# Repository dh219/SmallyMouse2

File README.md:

## Synopsis

SmallyMouse2 is the AT90USB1287 firmware source code and KiCAD schematic/PCB design for the SmallyMouse2 project.

Smalliermouse is a variation of SmallyMouse2 by D Henderson specificially designed for the Atari ST & Falcon to fit within the keyboard mouse plug bay.

## Motivation

SmallyMouse2 is a project that creates a USB mouse adaptor for retro computers that use quadrature mouse input including the Acorn BBC Micro, Acorn Master series, Commodore Amiga, Atari ST, busmouse compatible computers and many more.  SmallyMouse2 provides both a generic mouse output header (for attaching mouse to retro computer cables) and an IDC connector suitable for use with Acorn 8-bit user-ports.  SmallyMouse2 also features a configurable quadrature rate limiter that prevents VIA overrun when in use with slower 8-bit machines.

SmallyMouse2 supports both JTAG and USB bootloader programming.  The AT90USB1287 is pre-programmed by Atmel with the (FLIP) DFU bootloader; this bootloader is recognised by Atmel Studio as a programming device and can be used to flash the firmware to the board.

## Installation

Note: This is an Atmel Studio 7 project that can be loaded and compiled by the IDE

Please see http://www.waitingforfriday.com/?p=827 for detailed documentation about SmallyMouse2

## Author

SmallyMouse2 is written and maintained by Simon Inns

## License (Software)

    SmallyMouse2 is free software: you can redistribute it and/or modify
    it under the terms of the GNU General Public License as published by
    the Free Software Foundation, either version 3 of the License, or
    (at your option) any later version.

    SmallyMouse2 is distributed in the hope that it will be useful,
    but WITHOUT ANY WARRANTY; without even the implied warranty of
    MERCHANTABILITY or FITNESS FOR A PARTICULAR PURPOSE.  See the
    GNU General Public License for more details.

    You should have received a copy of the GNU General Public License
    along with SmallyMouse2. If not, see <http://www.gnu.org/licenses/>.

## License (Hardware)

Both the schematic and the PCB design of SmallyMouse2 (i.e. the KiCAD project and files) are covered by a Creative Commons license; as with the software you are welcome (and encouraged!) to extend, re-spin and otherwise use and modify the design as allowed by the license.  However; under the terms of the Attribution-ShareAlike 4.0 International (CC BY-SA 4.0) license you are required to release your design (or redesign) under the same license.  For details of the licensing requirements please see <https://creativecommons.org/licenses/by-sa/4.0/>

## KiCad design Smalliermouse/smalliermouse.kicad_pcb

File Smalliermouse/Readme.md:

## Synopsis

Smalliermouse is a variation of SmallyMouse2 by D Henderson specificially designed for the Atari ST & Falcon to fit within the keyboard mouse plug bay.

## Motivation

USB plugs for modern (and particularly wireless) devices are so small theses days that, buy reducing the SmallyMouse2 footprint to its bare minimum would allow the entire mouse emulator to fit within the below-keyboard recess of the Atari ST range of computers.

## Installation

Note: This is an Atmel Studio 7 project that can be loaded and compiled by the IDE

Please see http://www.waitingforfriday.com/?p=827 for detailed documentation about SmallyMouse2

## Author

SmallyMouse2 is written and maintained by Simon Inns. Smalliermouse, upon which it is based remains (C) Simon Inns with modifications by D Henderson 2019.

## License (Software)

    SmallyMouse2 is free software: you can redistribute it and/or modify
    it under the terms of the GNU General Public License as published by
    the Free Software Foundation, either version 3 of the License, or
    (at your option) any later version.

    SmallyMouse2 is distributed in the hope that it will be useful,
    but WITHOUT ANY WARRANTY; without even the implied warranty of
    MERCHANTABILITY or FITNESS FOR A PARTICULAR PURPOSE.  See the
    GNU General Public License for more details.

    You should have received a copy of the GNU General Public License
    along with SmallyMouse2. If not, see <http://www.gnu.org/licenses/>.

## License (Hardware)

Both the schematic and the PCB design of SmallyMouse2 (i.e. the KiCAD project and files) are covered by a Creative Commons license; as with the software you are welcome (and encouraged!) to extend, re-spin and otherwise use and modify the design as allowed by the license.  However; under the terms of the Attribution-ShareAlike 4.0 International (CC BY-SA 4.0) license you are required to release your design (or redesign) under the same license.  For details of the licensing requirements please see <https://creativecommons.org/licenses/by-sa/4.0/>

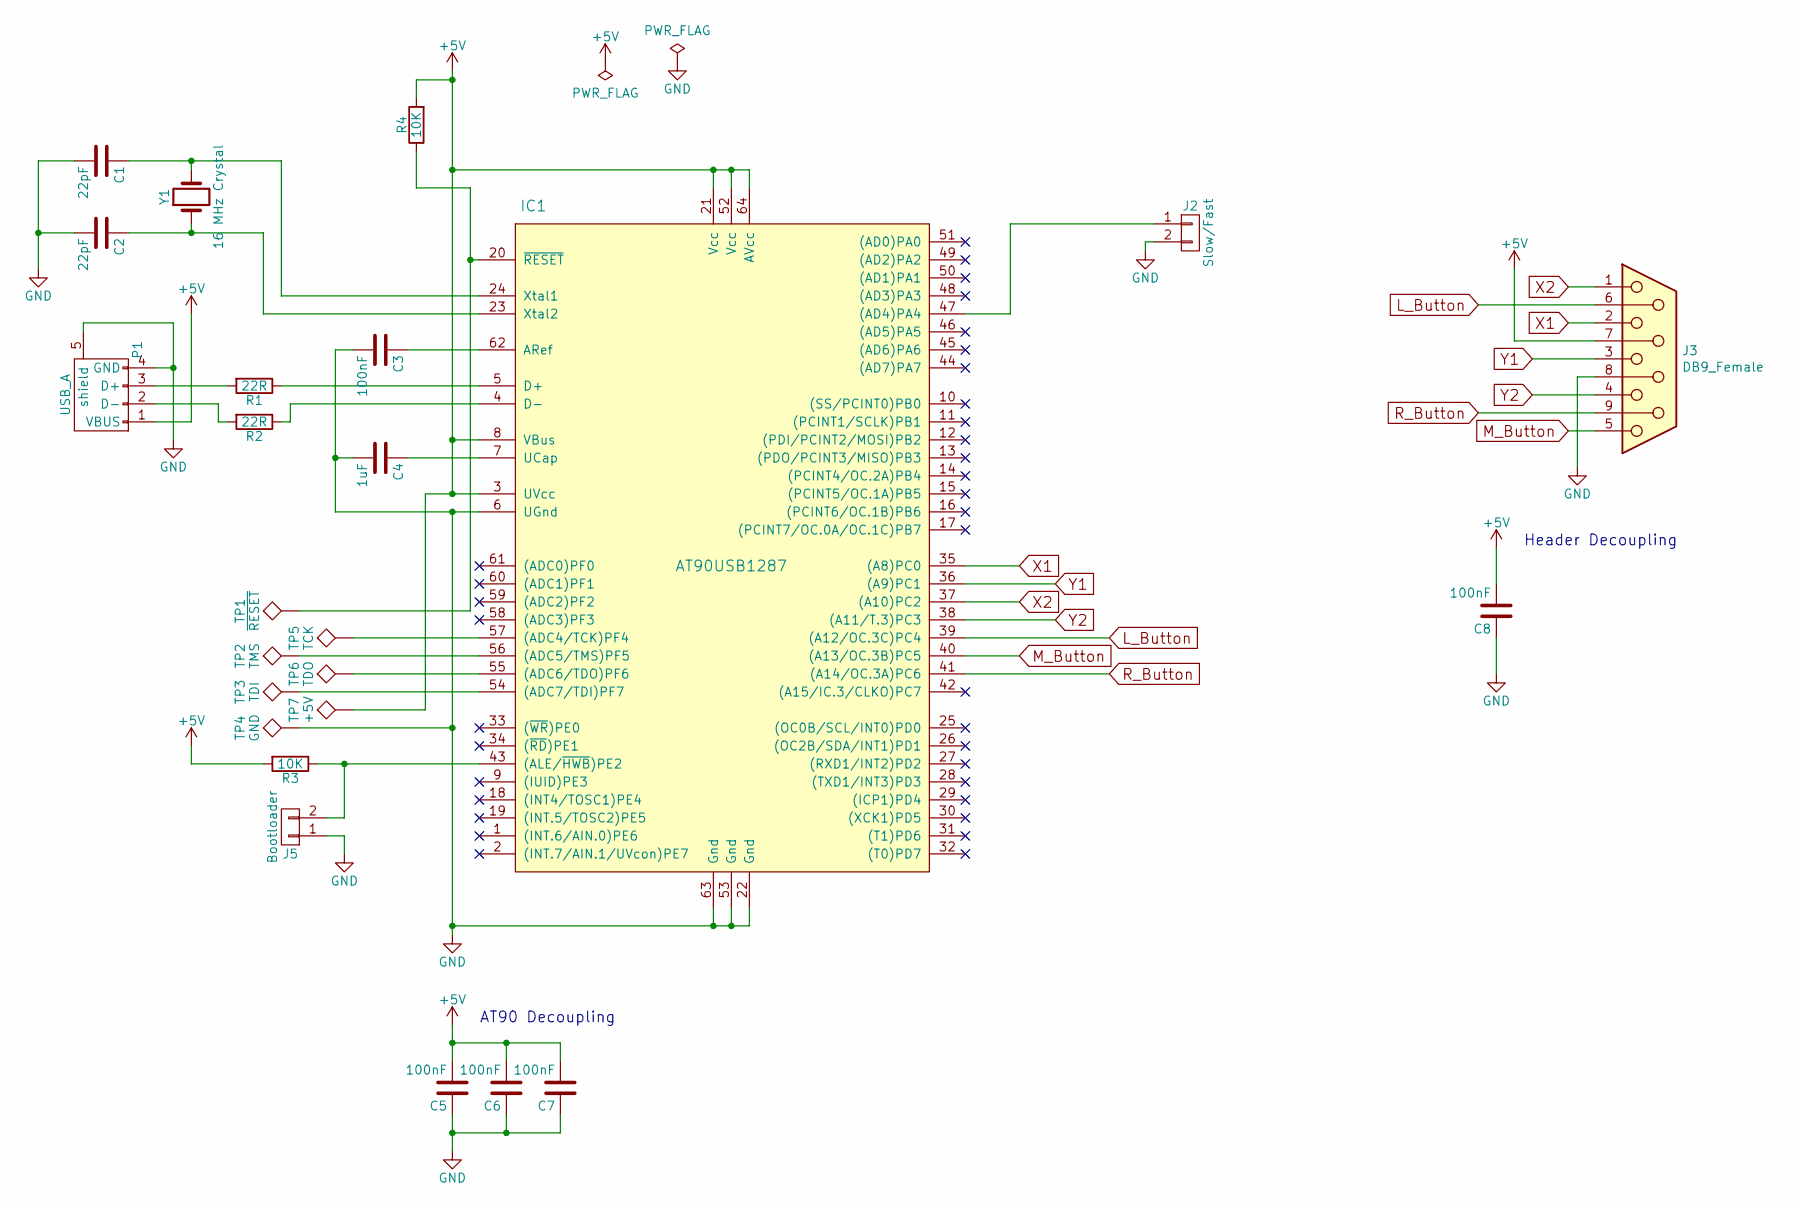
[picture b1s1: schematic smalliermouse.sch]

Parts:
C1, C2: 22pF; C_0805_2012Metric_Pad1.15x1.40mm_HandSolder
C3, C5, C6, C7, C8: 100nF; C_0805_2012Metric_Pad1.15x1.40mm_HandSolder
C4: 1uF; C_0805_2012Metric_Pad1.15x1.40mm_HandSolder
IC1: AT90USB1287; TQFP-64_14x14mm_P0.8mm
J2: Slow/Fast; PinHeader_1x02_P2.54mm_Vertical
J3: DB9_Female; DSUB-9_Female_EdgeMount_P2.77mm
J5: Bootloader; PinHeader_1x02_P2.54mm_Vertical
P1: USB_A; USB_A_CNCTech_1001-011-01101_Horizontal
R1, R2: 22R; R_0805_2012Metric_Pad1.15x1.40mm_HandSolder
R3, R4: 10K; R_0805_2012Metric_Pad1.15x1.40mm_HandSolder
TP1: ~RESET; TestPoint_Pad_1.0x1.0mm
TP2: TMS; TestPoint_Pad_1.0x1.0mm
TP3: TDI; TestPoint_Pad_1.0x1.0mm
TP4: GND; TestPoint_Pad_1.0x1.0mm
TP5: TCK; TestPoint_Pad_1.0x1.0mm
TP6: TDO; TestPoint_Pad_1.0x1.0mm
TP7: +5V; TestPoint_Pad_1.0x1.0mm
Y1: 16 MHz Crystal; Crystal_SMD_5032-2Pin_5.0x3.2mm_HandSoldering

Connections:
+5V: C5.2, C6.2, C7.2, C8.2, IC1.3 (UVcc), IC1.8 (VBus), IC1.21 (Vcc), IC1.52 (Vcc), IC1.64 (AVcc), J3.7, P1.1 (VBUS), R3.2, R4.2, TP7.1
GND: C1.2, C2.2, C3.2, C4.2, C5.1, C6.1, C7.1, C8.1, IC1.6 (UGnd), IC1.22 (Gnd), IC1.53 (Gnd), IC1.63 (Gnd), J2.2, J3.8, J5.1, P1.4 (GND), P1.5 (shield), TP4.1
L_Button: IC1.39 ((A12/OC.3C)PC4), J3.6
M_Button: IC1.40 ((A13/OC.3B)PC5), J3.5
unnamed: C1.1, IC1.24 (Xtal1), Y1.2
unnamed: C2.1, IC1.23 (Xtal2), Y1.1
unnamed: C3.1, IC1.62 (ARef)
unnamed: C4.1, IC1.7 (UCap)
unnamed: IC1.4 (D-), R2.1
unnamed: IC1.5 (D+), R1.1
unnamed: IC1.20 (~RESET), R4.1, TP1.1
unnamed: IC1.43 ((ALE/~HWB~)PE2), J5.2, R3.1
unnamed: IC1.47 ((AD4)PA4), J2.1
unnamed: IC1.54 ((ADC7/TDI)PF7), TP3.1
unnamed: IC1.55 ((ADC6/TDO)PF6), TP6.1
unnamed: IC1.56 ((ADC5/TMS)PF5), TP2.1
unnamed: IC1.57 ((ADC4/TCK)PF4), TP5.1
unnamed: P1.2 (D-), R2.2
unnamed: P1.3 (D+), R1.2
R_Button: IC1.41 ((A14/OC.3A)PC6), J3.9
X1: IC1.35 ((A8)PC0), J3.2
X2: IC1.37 ((A10)PC2), J3.1
Y1: IC1.36 ((A9)PC1), J3.3
Y2: IC1.38 ((A11/T.3)PC3), J3.4

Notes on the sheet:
AT90 Decoupling
Header Decoupling

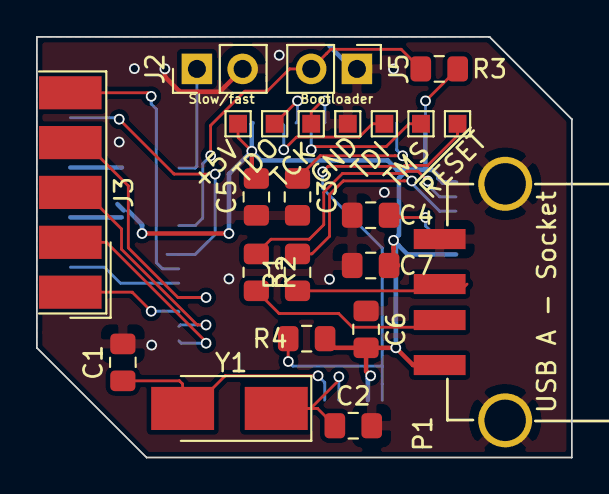
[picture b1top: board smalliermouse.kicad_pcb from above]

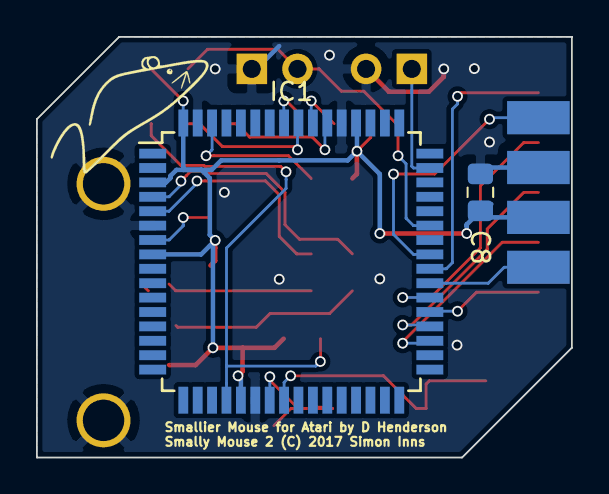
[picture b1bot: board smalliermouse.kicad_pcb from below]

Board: 2 copper layers, 29.7 x 23.4 mm, 25 parts (2 on the bottom side), 24 nets.

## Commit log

2019-11-28 Adding the release version of Smalliermouse
2019-11-28 Added some glamour shots
2019-12-06 Changed LB, RB and MB to High-Z (ie. input) when not clicked.
2019-12-07 Added prescaler for DPI correction
2019-12-08 Adding a binary firmware example
2019-12-31 Fixed DPISCALE logic -- introduced a skipped count to make sure the scaling works at very low levels.
2021-04-23 Closing the gap between SmallierMouse and SmallyMouse2. To wit:
    * Taken latest source incorporating fixes to direction lag and my suggested scaling.
    * Set ST-optimised values for the divisor, quad limit and buffer
    * Added my sub-pixel divisor logic
    * Made rate limiting the default
    * Swapped the pins for the divisor and rate limit headers as SmallierMouse was designed before this header was available and frankly removing the limit is madness on an ST
2021-04-29 Providing a couple of sample binaries ready for release 1.1

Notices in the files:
Smalliermouse/smalliermouse.kicad_pcb:
(c) 2017 Simon Inns; modified 2019 by D Henderson
License: Attribution-ShareAlike 4.0 International (CC BY-SA 4.0)
Smally Mouse 2 (C) 2017 Simon Inns
